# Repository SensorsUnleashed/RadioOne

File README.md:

# RadioOne
cc2538 based radio board using an XBee footprint.

Rev B.

Ready for prototype fabrication.

#

#

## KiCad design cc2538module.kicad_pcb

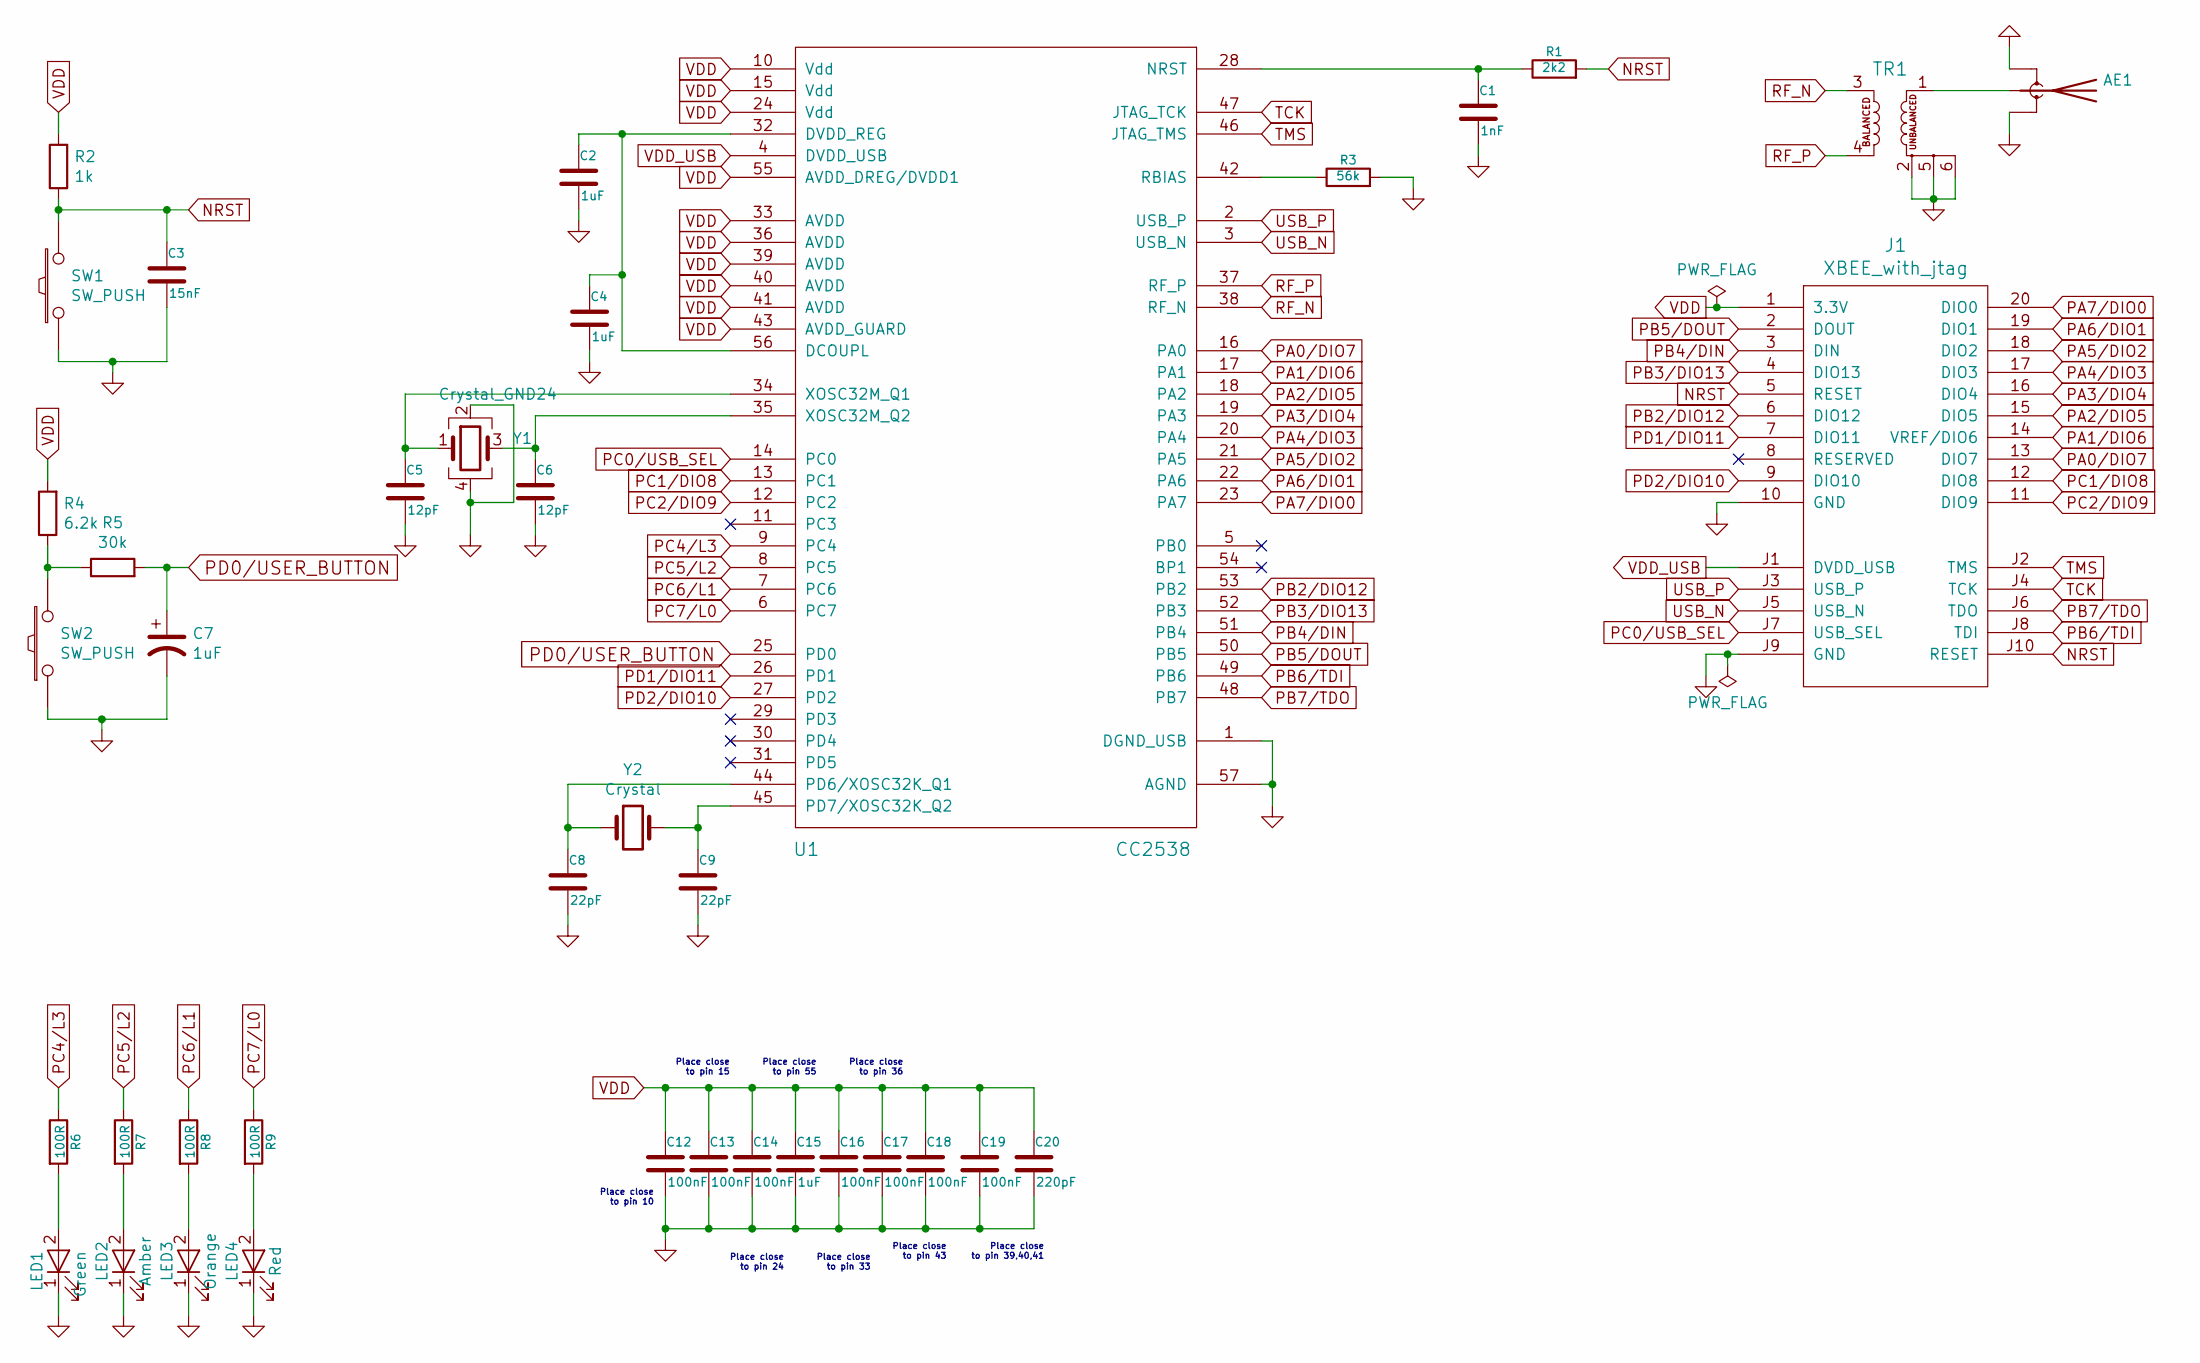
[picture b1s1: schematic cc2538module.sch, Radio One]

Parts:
AE1: Antenna_Shield_3pin; Antenna_Ext_3pin_smd; Manufacturer Part Number RECE.20279.001E.01
C1: 1nF; C_0402_1005Metric; Manufacturer Part Number GRM155R71H102KA01D
C2, C4, C15: 1uF; C_0402_1005Metric; Manufacturer Part Number GRM155R61A105KE01D
C3: 15nF; C_0402_1005Metric; Manufacturer Part Number GRM155R71H153KA12J
C5, C6: 12pF; C_0402_1005Metric; Manufacturer Part Number GRM1555C1H120JA01D
C7: 1uF; C_0402_1005Metric
C8, C9: 22pF; C_0402_1005Metric; Manufacturer Part Number GRM1555C1H220JA01J
C12, C13, C14, C16, C17, C18, C19: 100nF; C_0402_1005Metric; Manufacturer Part Number GRM155R70J104KA01D
C20: 220pF; C_0402_1005Metric; Manufacturer Part Number GRM1555C1H221JA01D
J1: XBEE_with_jtag; XBEE-HEADER_with_JTAG; Manufacturer Part Number M50-3600542+
LED1: Green; LED_0402_1005Metric; Manufacturer Part Number LNJ347W83RA
LED2: Amber; LED_0402_1005Metric; Manufacturer Part Number LNJ447W84RA1
LED3: Orange; LED_0402_1005Metric; Manufacturer Part Number LNJ847W83RA
LED4: Red; LED_0402_1005Metric; Manufacturer Part Number LNJ247W82RA
R1: 2k2; R_0402_1005Metric; Manufacturer Part Number RC0402FR-072K2L
R2: 1k; R_0402_1005Metric; Manufacturer Part Number RC0402FR-071KL
R3: 56k; R_0402_1005Metric; Manufacturer Part Number RC0402FR-0756KL
R4: 6.2k; R_0402_1005Metric; Manufacturer Part Number RC0402FR-076K2L
R5: 30k; R_0402_1005Metric; Manufacturer Part Number RC0402FR-0730KL
R6, R7, R8, R9: 100R; R_0402_1005Metric; Manufacturer Part Number RC0402FR-07100RL
SW1, SW2: SW_PUSH; SW_SPST_B3U-1000P-B; Manufacturer Part Number B3U-1000P-B
TR1: BALUN_2450BM15A0002; BALUM_2450BM15A0002; Manufacturer Part Number 2450BM15A0002E
U1: CC2538; cc2538_QFN_56; Manufacturer Part Number CC2538NF53RTQR
Y1: Crystal_GND24; Crystal_SMD_2016-4Pin_2.0x1.6mm; Manufacturer Part Number FA-128 32.0000MF20X-K5
Y2: Crystal; Crystal_SMD_2012-2Pin_2.0x1.2mm; Manufacturer Part Number FC-12M 32.7680KA-A5

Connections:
GND: AE1.2 (Shield), C1.2, C2.2, C3.2, C4.2, C5.2, C6.2, C7.2, C8.2, C9.2, C12.2, C13.2, C14.2, C15.2, C16.2, C17.2, C18.2, C19.2, C20.2, J1.10 (GND), J1.J9 (GND), LED1.1 (K), LED2.1 (K), LED3.1 (K), LED4.1 (K), R3.2, SW1.1, SW2.1, TR1.2, TR1.5, TR1.6, U1.1 (DGND_USB), U1.57 (AGND), Y1.2, Y1.4
NRST: C3.1, J1.5 (RESET), J1.J10 (RESET), R1.2, R2.1, SW1.2
unnamed: AE1.1 (A), TR1.1
unnamed: C1.1, R1.1, U1.28 (NRST)
unnamed: C2.1, C4.1, U1.32 (DVDD_REG), U1.56 (DCOUPL)
unnamed: C5.1, U1.34 (XOSC32M_Q1), Y1.1
unnamed: C6.1, U1.35 (XOSC32M_Q2), Y1.3
unnamed: C8.1, U1.44 (PD6/XOSC32K_Q1), Y2.1
unnamed: C9.1, U1.45 (PD7/XOSC32K_Q2), Y2.2
unnamed: LED1.2 (A), R6.2
unnamed: LED2.2 (A), R7.2
unnamed: LED3.2 (A), R8.2
unnamed: LED4.2 (A), R9.2
unnamed: R3.1, U1.42 (RBIAS)
unnamed: R4.1, R5.1, SW2.2
PA0/DIO7: J1.13 (DIO7), U1.16 (PA0)
PA1/DIO6: J1.14 (VREF/DIO6), U1.17 (PA1)
PA2/DIO5: J1.15 (DIO5), U1.18 (PA2)
PA3/DIO4: J1.16 (DIO4), U1.19 (PA3)
PA4/DIO3: J1.17 (DIO3), U1.20 (PA4)
PA5/DIO2: J1.18 (DIO2), U1.21 (PA5)
PA6/DIO1: J1.19 (DIO1), U1.22 (PA6)
PA7/DIO0: J1.20 (DIO0), U1.23 (PA7)
PB2/DIO12: J1.6 (DIO12), U1.53 (PB2)
PB3/DIO13: J1.4 (DIO13), U1.52 (PB3)
PB4/DIN: J1.3 (DIN), U1.51 (PB4)
PB5/DOUT: J1.2 (DOUT), U1.50 (PB5)
PB6/TDI: J1.J8 (TDI), U1.49 (PB6)
PB7/TDO: J1.J6 (TDO), U1.48 (PB7)
PC0/USB_SEL: J1.J7 (USB_SEL), U1.14 (PC0)
PC1/DIO8: J1.12 (DIO8), U1.13 (PC1)
PC2/DIO9: J1.11 (DIO9), U1.12 (PC2)
PC4/L3: R6.1, U1.9 (PC4)
PC5/L2: R7.1, U1.8 (PC5)
PC6/L1: R8.1, U1.7 (PC6)
PC7/L0: R9.1, U1.6 (PC7)
PD0/USER_BUTTON: C7.1, R5.2, U1.25 (PD0)
PD1/DIO11: J1.7 (DIO11), U1.26 (PD1)
PD2/DIO10: J1.9 (DIO10), U1.27 (PD2)
RF_N: TR1.3, U1.38 (RF_N)
RF_P: TR1.4, U1.37 (RF_P)
TCK: J1.J4 (TCK), U1.47 (JTAG_TCK)
TMS: J1.J2 (TMS), U1.46 (JTAG_TMS)
USB_N: J1.J5 (USB_N), U1.3 (USB_N)
USB_P: J1.J3 (USB_P), U1.2 (USB_P)
VDD: C12.1, C13.1, C14.1, C15.1, C16.1, C17.1, C18.1, C19.1, C20.1, J1.1 (3.3V), R2.2, R4.2, U1.10 (Vdd), U1.15 (Vdd), U1.24 (Vdd), U1.33 (AVDD), U1.36 (AVDD), U1.39 (AVDD), U1.40 (AVDD), U1.41 (AVDD), U1.43 (AVDD_GUARD), U1.55 (AVDD_DREG/DVDD1)
VDD_USB: J1.J1 (DVDD_USB), U1.4 (DVDD_USB)

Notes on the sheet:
Place close to pin 10
Place close to pin 15
Place close to pin 24
Place close to pin 55
Place close to pin 33
Place close to pin 39,40,41
Place close to pin 36
Place close to pin 43

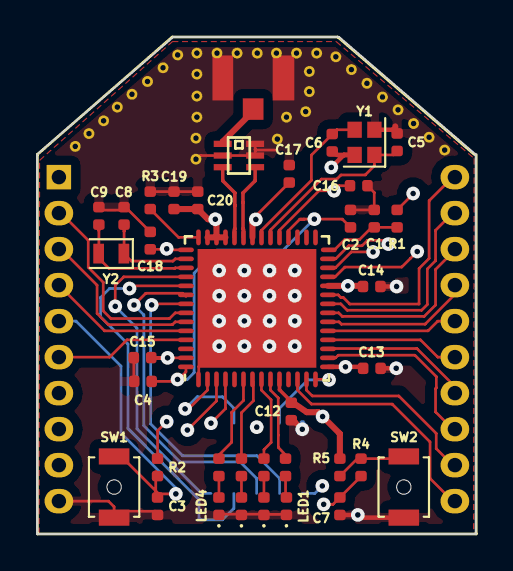
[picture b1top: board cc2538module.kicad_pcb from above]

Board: 4 copper layers, 24.4 x 27.6 mm, 39 parts (0 on the bottom side), 47 nets.

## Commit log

2017-03-06 Board rev.1 finished and send to DirtyPCB for prototyping
2017-03-12 Updated component infos
2017-03-14 Changed the header description
2017-03-14 Added a gitignore file
2017-03-19 Added C5 to PCB and rearrange the step down power converter as described in its datasheet
2017-03-29 New footprint and various small changes. PCB ordered at DirtyPCB 20170328
2017-03-29 Added untracked files to gitignore
2017-04-18 Print has arrived, images added
2018-10-22 Rev B
2018-10-22 Made paths relavtive to the project dir
2018-10-22 Removed old files not valid for rev B
2018-10-22 Updated the readme
